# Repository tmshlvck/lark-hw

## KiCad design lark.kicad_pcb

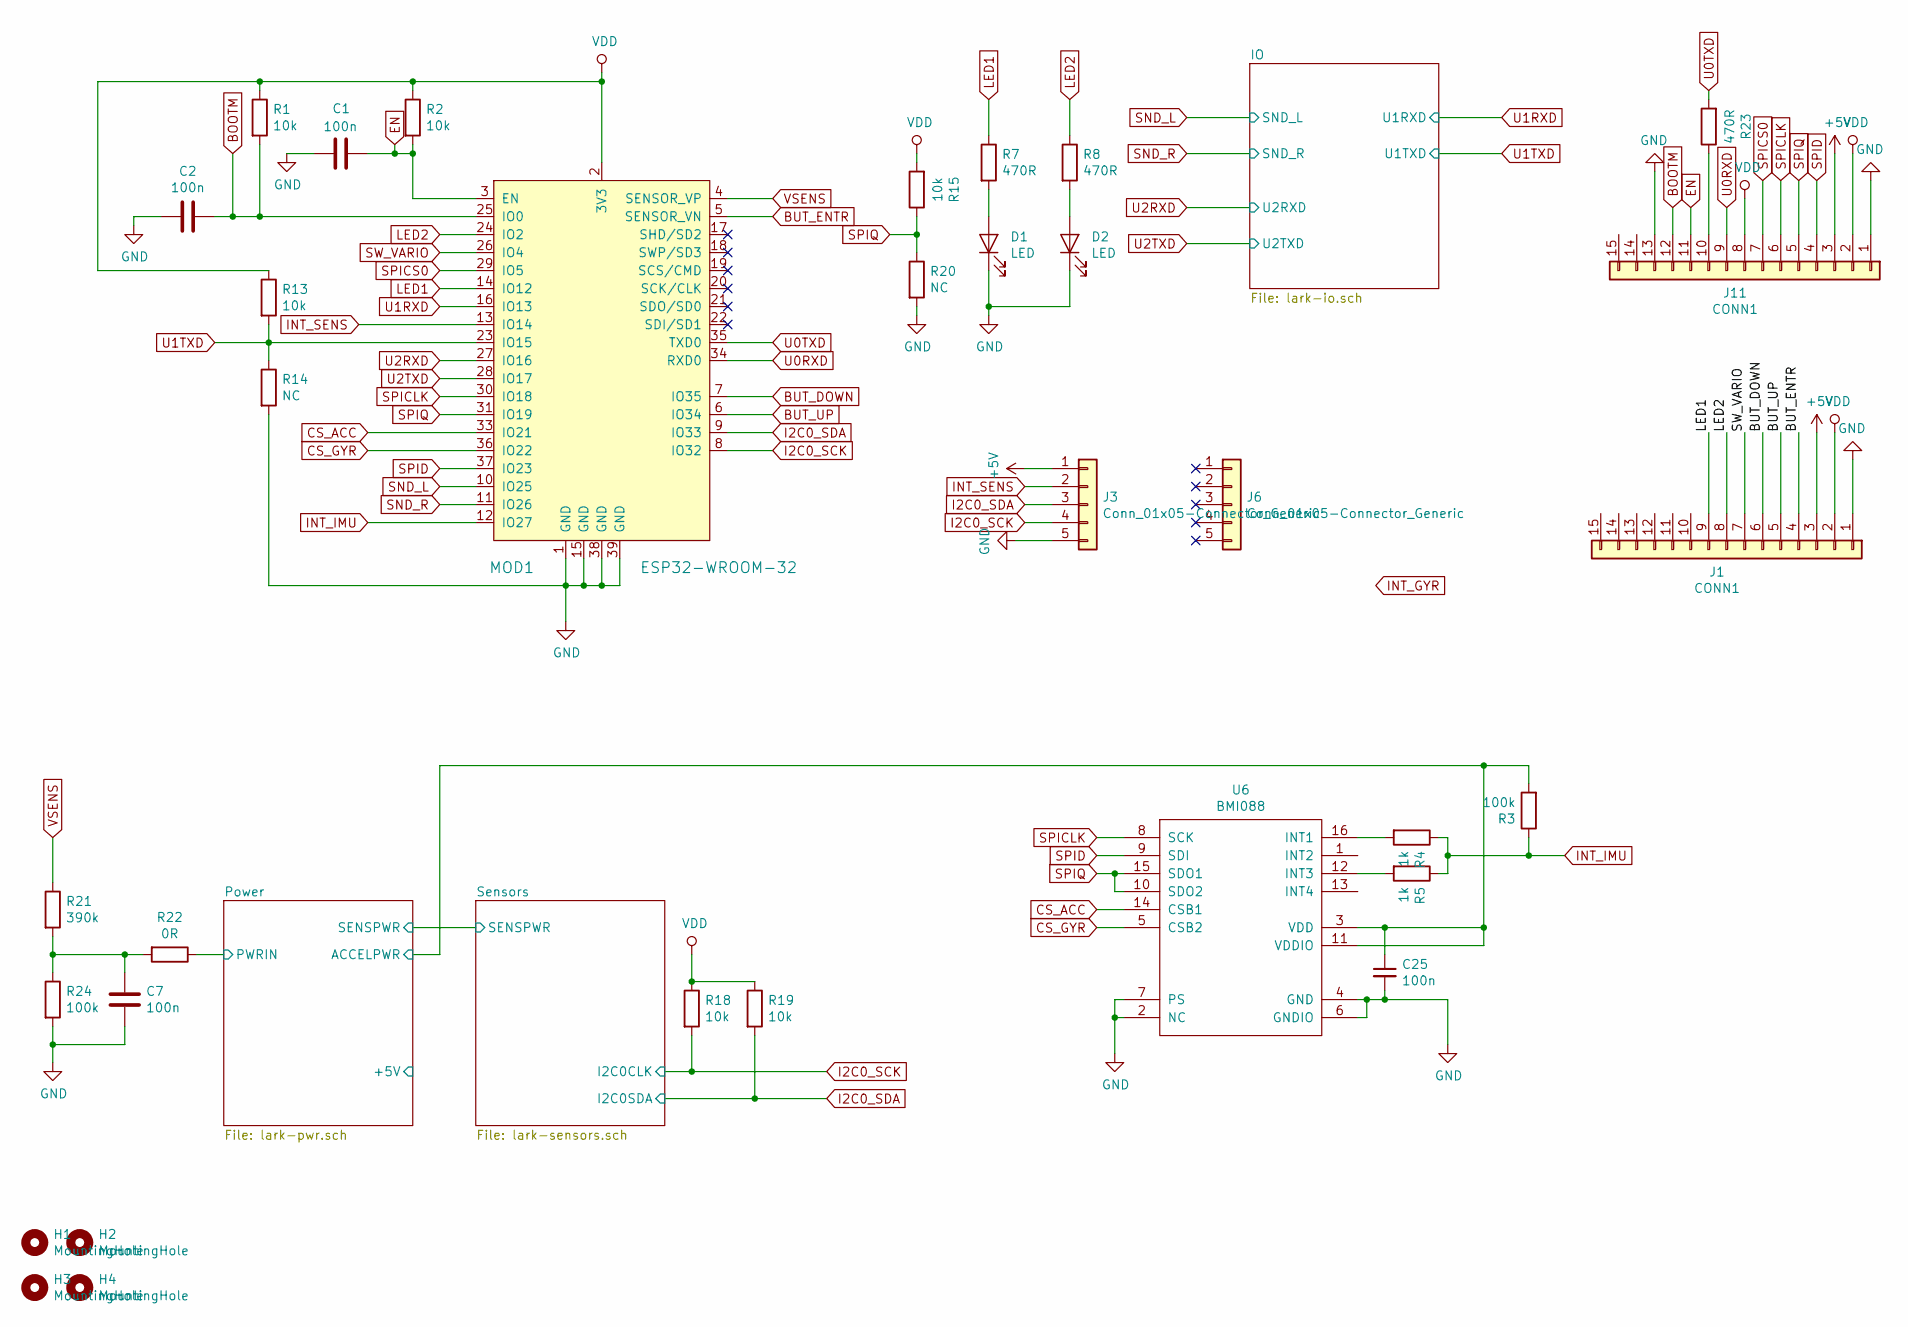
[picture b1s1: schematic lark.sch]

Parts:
C1, C2, C7: 100n; C_0805_2012Metric_Pad1.15x1.40mm_HandSolder; MPN 885012207128
C25: 100n; C_0805_2012Metric_Pad1.15x1.40mm_HandSolder
D1: LED; LED_1206_3216Metric_Pad1.42x1.75mm_HandSolder; MPN LTST-C150GKT
D2: LED; LED_1206_3216Metric_Pad1.42x1.75mm_HandSolder; MPN LTST-C150CKT
H1, H2, H3, H4: MountingHole; MountingHole_3.2mm_M3_DIN965
J1, J11: CONN1; PinHeader_1x15_P2.54mm_Vertical
J3, J6: Conn_01x05-Connector_Generic; PinHeader_1x05_P2.54mm_Vertical
MOD1: ESP32-WROOM-32; ESP32-WROOM-32D; MPN ESP32-WROOM-32; Digi-Key_PN 1904-1010-1-ND
R1, R2, R13, R15, R18, R19: 10k; R_0805_2012Metric_Pad1.15x1.40mm_HandSolder; MPN RC0805FR-0710KL
R3: 100k; R_0805_2012Metric_Pad1.15x1.40mm_HandSolder
R4, R5: 1k; R_0805_2012Metric_Pad1.15x1.40mm_HandSolder
R7, R8, R23: 470R; R_0805_2012Metric_Pad1.15x1.40mm_HandSolder; MPN RC0805FR-07470RL
R14, R20: NC; R_0805_2012Metric_Pad1.15x1.40mm_HandSolder
R21: 390k; R_0805_2012Metric_Pad1.15x1.40mm_HandSolder; MPN RT0805BRD07390KL
R22: 0R; R_0805_2012Metric_Pad1.15x1.40mm_HandSolder; MPN RC0805JR-070RL
R24: 100k; R_0805_2012Metric_Pad1.15x1.40mm_HandSolder; MPN RT0805BRD07100KL
U6: BMI088; LGA-16_handsolder

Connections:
+5V: J1.3, J3.1, J11.3; also elsewhere on the board
/Power/ACCELPWR: C25.1, R3.2, U6.3 (VDD), U6.11 (VDDIO); also elsewhere on the board
BOOTM: C2.1, J11.12, MOD1.25 (IO0), R1.2
BUT_DOWN: J1.6, MOD1.7 (IO35)
BUT_ENTR: J1.4, MOD1.5 (SENSOR_VN)
BUT_UP: J1.5, MOD1.6 (IO34)
CS_ACC: MOD1.33 (IO21), U6.14 (CSB1)
CS_GYR: MOD1.36 (IO22), U6.5 (CSB2)
EN: C1.1, J11.11, MOD1.3 (EN), R2.2
GND: C1.2, C2.2, C7.2, C25.2, D1.1 (K), D2.1 (K), J1.1, J3.5, J11.1, J11.13, MOD1.1 (GND), MOD1.15 (GND), MOD1.38 (GND), MOD1.39 (GND), R14.2, R20.2, R24.2, U6.2 (NC), U6.4 (GND), U6.6 (GNDIO), U6.7 (PS); also elsewhere on the board
I2C0_SCK: J3.4, MOD1.8 (IO32), R18.2; also elsewhere on the board
I2C0_SDA: J3.3, MOD1.9 (IO33), R19.2; also elsewhere on the board
INT_IMU: MOD1.12 (IO27), R3.1, R4.1, R5.1
INT_SENS: J3.2, MOD1.13 (IO14)
LED1: J1.9, MOD1.14 (IO12), R7.1
LED2: J1.8, MOD1.24 (IO2), R8.1
unnamed: C7.1, R21.2, R22.2, R24.1
unnamed: D1.2 (A), R7.2
unnamed: D2.2 (A), R8.2
unnamed: J11.10, R23.1
unnamed: R4.2, U6.16 (INT1)
unnamed: R5.2, U6.12 (INT3)
SND_L: MOD1.10 (IO25); also elsewhere on the board
SND_R: MOD1.11 (IO26); also elsewhere on the board
SPICLK: J11.6, MOD1.30 (IO18), U6.8 (SCK)
SPICS0: J11.7, MOD1.29 (IO5)
SPID: J11.4, MOD1.37 (IO23), U6.9 (SDI)
SPIQ: J11.5, MOD1.31 (IO19), R15.1, R20.1, U6.10 (SDO2), U6.15 (SDO1)
SW_VARIO: J1.7, MOD1.26 (IO4)
U0RXD: J11.9, MOD1.34 (RXD0)
U0TXD: MOD1.35 (TXD0), R23.2
U1RXD: MOD1.16 (IO13); also elsewhere on the board
U1TXD: MOD1.23 (IO15), R13.2, R14.1; also elsewhere on the board
U2RXD: MOD1.27 (IO16); also elsewhere on the board
U2TXD: MOD1.28 (IO17); also elsewhere on the board
VDD: J1.2, J11.2, J11.8, MOD1.2 (3V3), R1.1, R2.1, R13.1, R15.2, R18.1, R19.1; also elsewhere on the board
VSENS: MOD1.4 (SENSOR_VP), R21.1

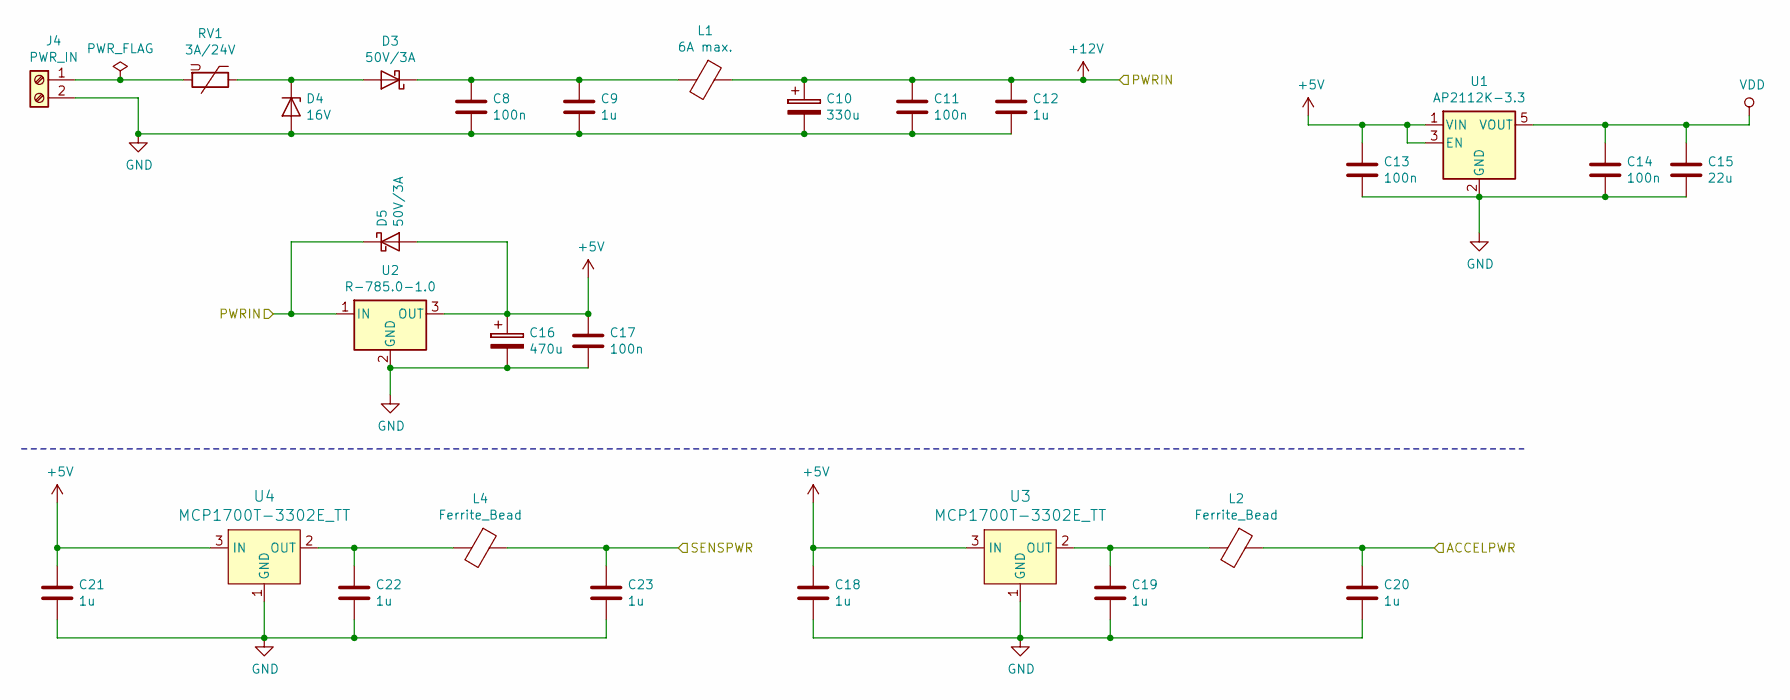
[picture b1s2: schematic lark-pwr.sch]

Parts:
C8, C11, C13, C14, C17: 100n; C_0805_2012Metric_Pad1.15x1.40mm_HandSolder; MPN 885012207128
C9, C12, C18, C19, C20, C21, C22, C23: 1u; C_0805_2012Metric_Pad1.15x1.40mm_HandSolder; MPN CL21B105KBFNNNG
C10: 330u; CP_Elec_10x10; MPN UUE1H331MNS1MS
C15: 22u; C_0805_2012Metric_Pad1.15x1.40mm_HandSolder; MPN GRM21BD70J226ME44L
C16: 470u; CP_Elec_10x10; MPN 493-16063-1-ND
D3, D5: 50V/3A; D_SOD-123; MPN SK35
D4: 16V; D_SOD-123; MPN SMBJ16A-TR
J4: PWR_IN; TerminalBlock_Phoenix_PT-1,5-2-3.5-H_1x02_P3.50mm_Horizontal; MPN 277-1721-ND
L1: 6A max.; L_1206_3216Metric_Pad1.42x1.75mm_HandSolder; MPN BLM31KN121SN1L
L2, L4: Ferrite_Bead; L_0805_2012Metric_Pad1.15x1.40mm_HandSolder; MPN BLM21BD272SH1L
RV1: 3A/24V; Fuse_2920_7451Metric_Pad2.10x5.45mm_HandSolder; MPN 0ZCF0300BF2C
U1: AP2112K-3.3; SOT-23-5
U2: R-785.0-1.0; Converter_DCDC_RECOM_R-78E-0.5_THT
U3, U4: MCP1700T-3302E_TT; SOT-23; MPN MCP1700T-3302E/TT; Digi-Key_PN MCP1700T3302ETTCT-ND

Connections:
+5V: C13.1, C16.1, C17.1, C18.1, C21.1, D5.2 (A), U1.1 (VIN), U1.3 (EN), U2.3 (OUT), U3.3 (IN), U4.3 (IN); also elsewhere on the board
/Power/ACCELPWR: C20.1, L2.1; also elsewhere on the board
/Sensors/SENSPWR: C23.1, L4.1; also elsewhere on the board
GND: C8.2, C9.2, C10.2, C11.2, C12.2, C13.2, C14.2, C15.2, C16.2, C17.2, C18.2, C19.2, C20.2, C21.2, C22.2, C23.2, D4.2 (A), J4.2, U1.2 (GND), U2.2 (GND), U3.1 (GND), U4.1 (GND); also elsewhere on the board
unnamed: C19.1, L2.2, U3.2 (OUT)
unnamed 43: J4.1, RV1.2; also elsewhere on the board
VDD: C14.1, C15.1, U1.5 (VOUT); also elsewhere on the board

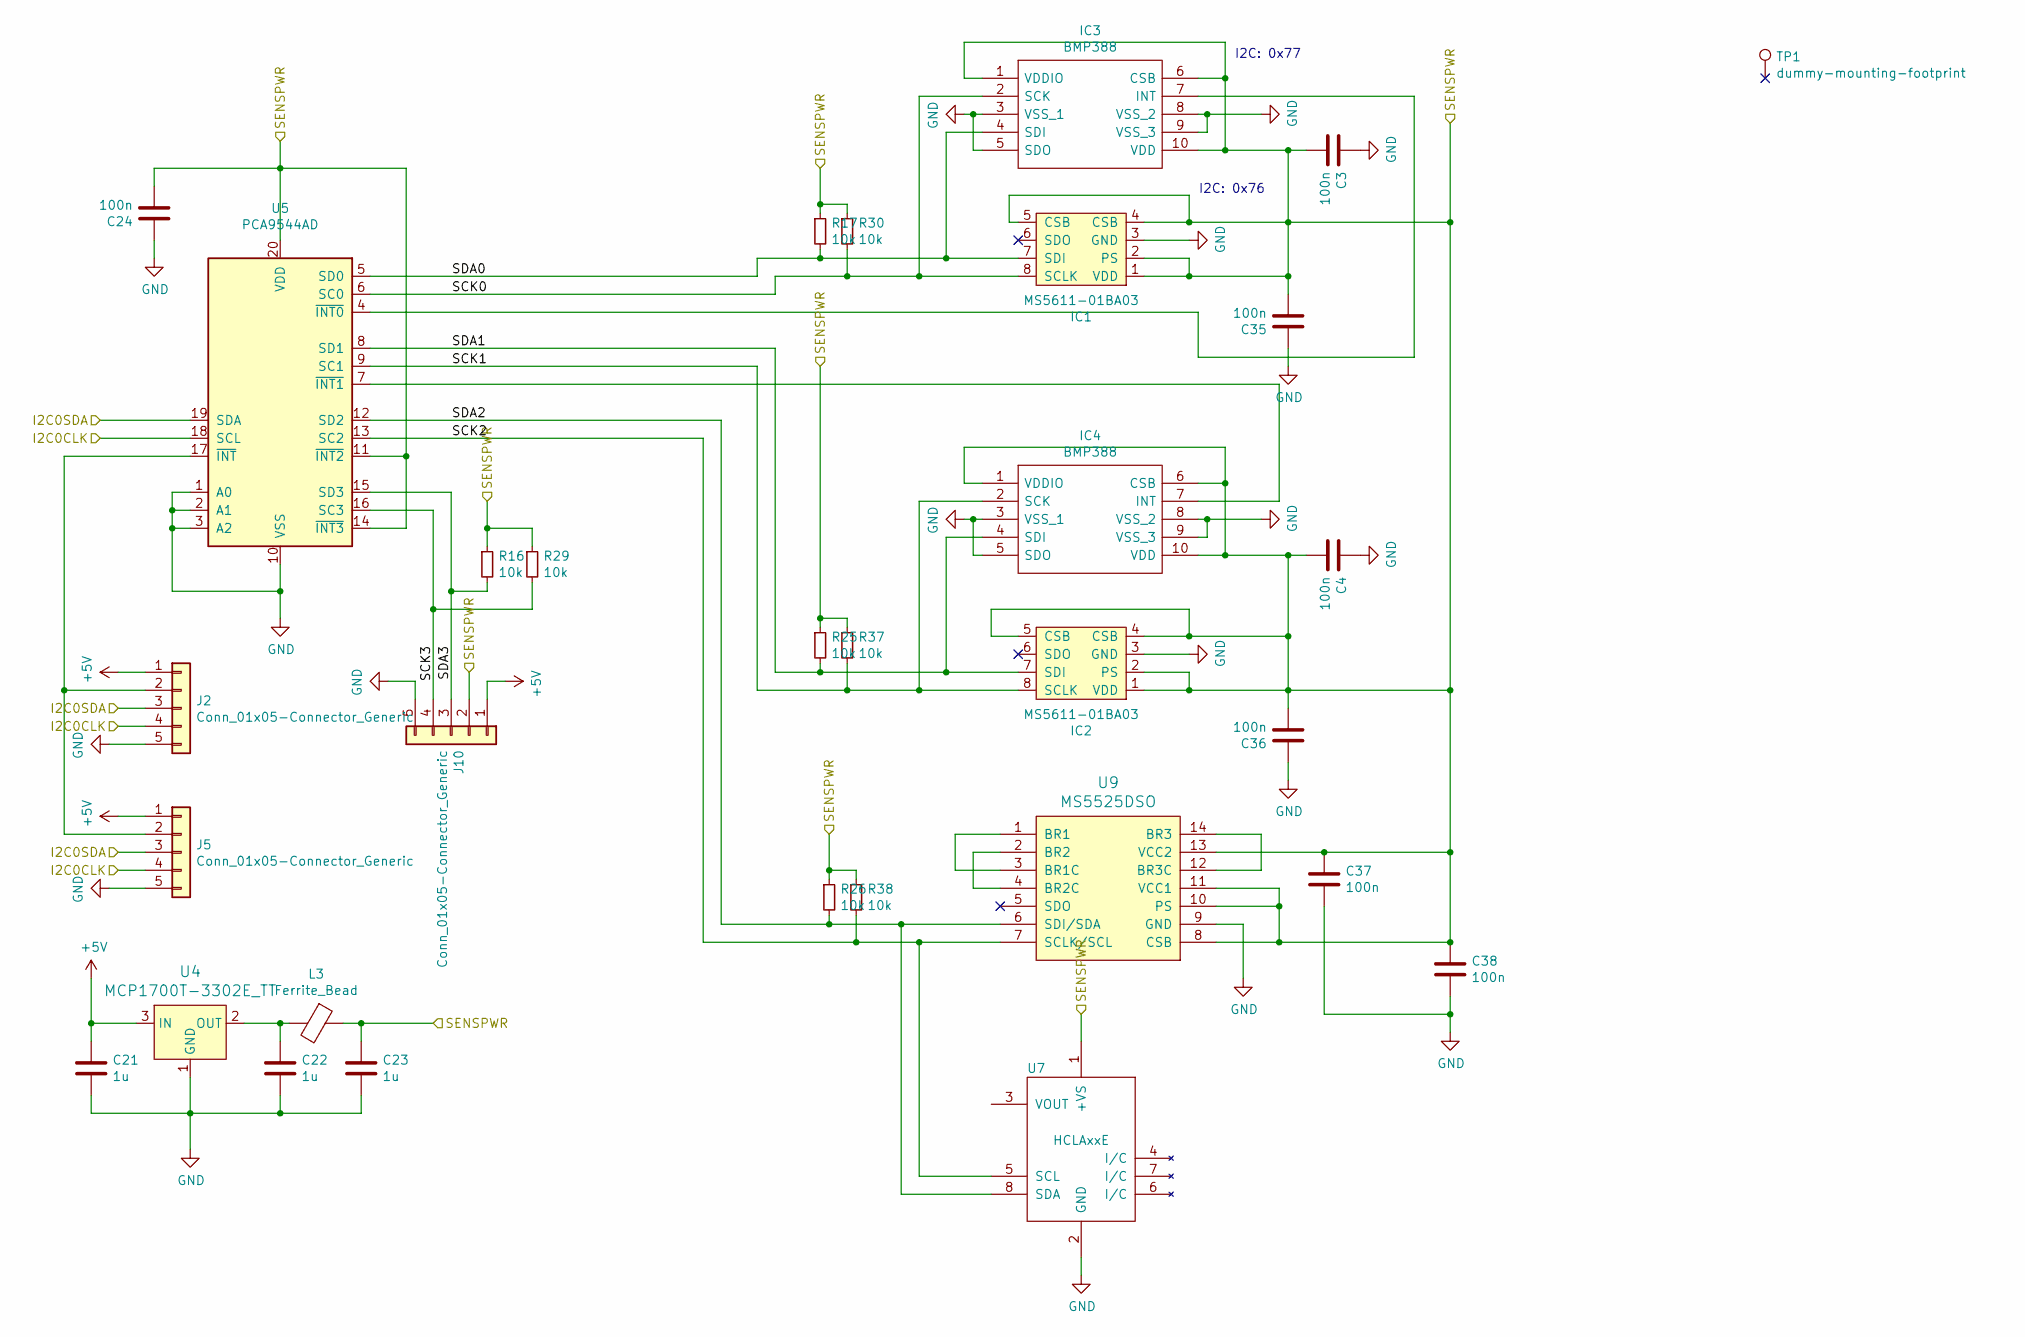
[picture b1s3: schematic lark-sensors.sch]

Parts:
C3, C4: 100n; C_0603_1608Metric; MPN 885012207128
C21, C22, C23: 1u; C_0805_2012Metric_Pad1.15x1.40mm_HandSolder; MPN CL21B105KBFNNNG
C24, C35, C36, C37, C38: 100n; C_0805_2012Metric_Pad1.15x1.40mm_HandSolder; MPN 885012207128
IC1, IC2: MS5611-01BA03; LGA-8_3x5mm_P1.25mm_handsolder; MPN MS561101BA03-50; Farnell 2362662
IC3, IC4: BMP388; LGA-10_2.0x2.0x0.75_handsolder; Manufacturer_Part_Number BMP388; Mouser Part Number 262-BMP388
J2, J5, J10: Conn_01x05-Connector_Generic; PinHeader_1x05_P2.54mm_Vertical
L3: Ferrite_Bead; L_0805_2012Metric_Pad1.15x1.40mm_HandSolder; MPN BLM21BD272SH1L
R16, R17, R25, R26, R29, R30, R37, R38: 10k; R_0805_2012Metric_Pad1.15x1.40mm_HandSolder
TP1: dummy-mounting-footprint; lark_sensor_mount
U4: MCP1700T-3302E_TT; SOT-23; MPN MCP1700T-3302E/TT; Digi-Key_PN MCP1700T3302ETTCT-ND
U5: PCA9544AD; SOIC-20W_7.5x12.8mm_P1.27mm
U7: HCLAxxE
U9: MS5525DSO; SOIC-14W_7.5x9.0mm_P1.27mm; MPN 5525DSO-DB001DS

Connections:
+5V: C21.1, J2.1, J5.1, J10.1, U4.3 (IN); also elsewhere on the board
/Sensors/SCK0: IC1.8 (SCLK), IC3.2 (SCK), R30.2, U5.6 (SC0)
/Sensors/SCK1: IC2.8 (SCLK), IC4.2 (SCK), R37.2, U5.9 (SC1)
/Sensors/SCK2: R38.2, U5.13 (SC2), U7.5 (SCL), U9.7 (SCLK/SCL)
/Sensors/SCK3: J10.4, R29.2, U5.16 (SC3)
/Sensors/SDA0: IC1.7 (SDI), IC3.4 (SDI), R17.2, U5.5 (SD0)
/Sensors/SDA1: IC2.7 (SDI), IC4.4 (SDI), R25.2, U5.8 (SD1)
/Sensors/SDA2: R26.2, U5.12 (SD2), U7.8 (SDA), U9.6 (SDI/SDA)
/Sensors/SDA3: J10.3, R16.2, U5.15 (SD3)
/Sensors/SENSPWR: C3.2, C4.2, C23.1, C24.2, C35.2, C36.2, C37.1, C38.1, IC1.1 (VDD), IC1.2 (PS), IC1.4 (CSB), IC1.5 (CSB), IC2.1 (VDD), IC2.2 (PS), IC2.4 (CSB), IC2.5 (CSB), IC3.1 (VDDIO), IC3.6 (CSB), IC3.10 (VDD), IC4.1 (VDDIO), IC4.6 (CSB), IC4.10 (VDD), J10.2, L3.1, R16.1, R17.1, R25.1, R26.1, R29.1, R30.1, R37.1, R38.1, U5.11 (~INT2), U5.14 (~INT3), U5.20 (VDD), U7.1 (+VS), U9.8 (CSB), U9.10 (PS), U9.11 (VCC1), U9.13 (VCC2); also elsewhere on the board
GND: C3.1, C4.1, C21.2, C22.2, C23.2, C24.1, C35.1, C36.1, C37.2, C38.2, IC1.3 (GND), IC2.3 (GND), IC3.3 (VSS_1), IC3.5 (SDO), IC3.8 (VSS_2), IC3.9 (VSS_3), IC4.3 (VSS_1), IC4.5 (SDO), IC4.8 (VSS_2), IC4.9 (VSS_3), J2.5, J5.5, J10.5, U4.1 (GND), U5.1 (A0), U5.2 (A1), U5.3 (A2), U5.10 (VSS), U7.2 (GND), U9.9 (GND); also elsewhere on the board
I2C0_SCK: J2.4, J5.4, U5.18 (SCL); also elsewhere on the board
I2C0_SDA: J2.3, J5.3, U5.19 (SDA); also elsewhere on the board
unnamed: IC3.7 (INT), U5.4 (~INT0)
unnamed: IC4.7 (INT), U5.7 (~INT1)
unnamed: J2.2, J5.2, U5.17 (~INT)
unnamed: U9.1 (BR1), U9.3 (BR1C)
unnamed: U9.2 (BR2), U9.4 (BR2C)
unnamed: U9.12 (BR3C), U9.14 (BR3)

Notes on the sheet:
I2C: 0x77
I2C: 0x76

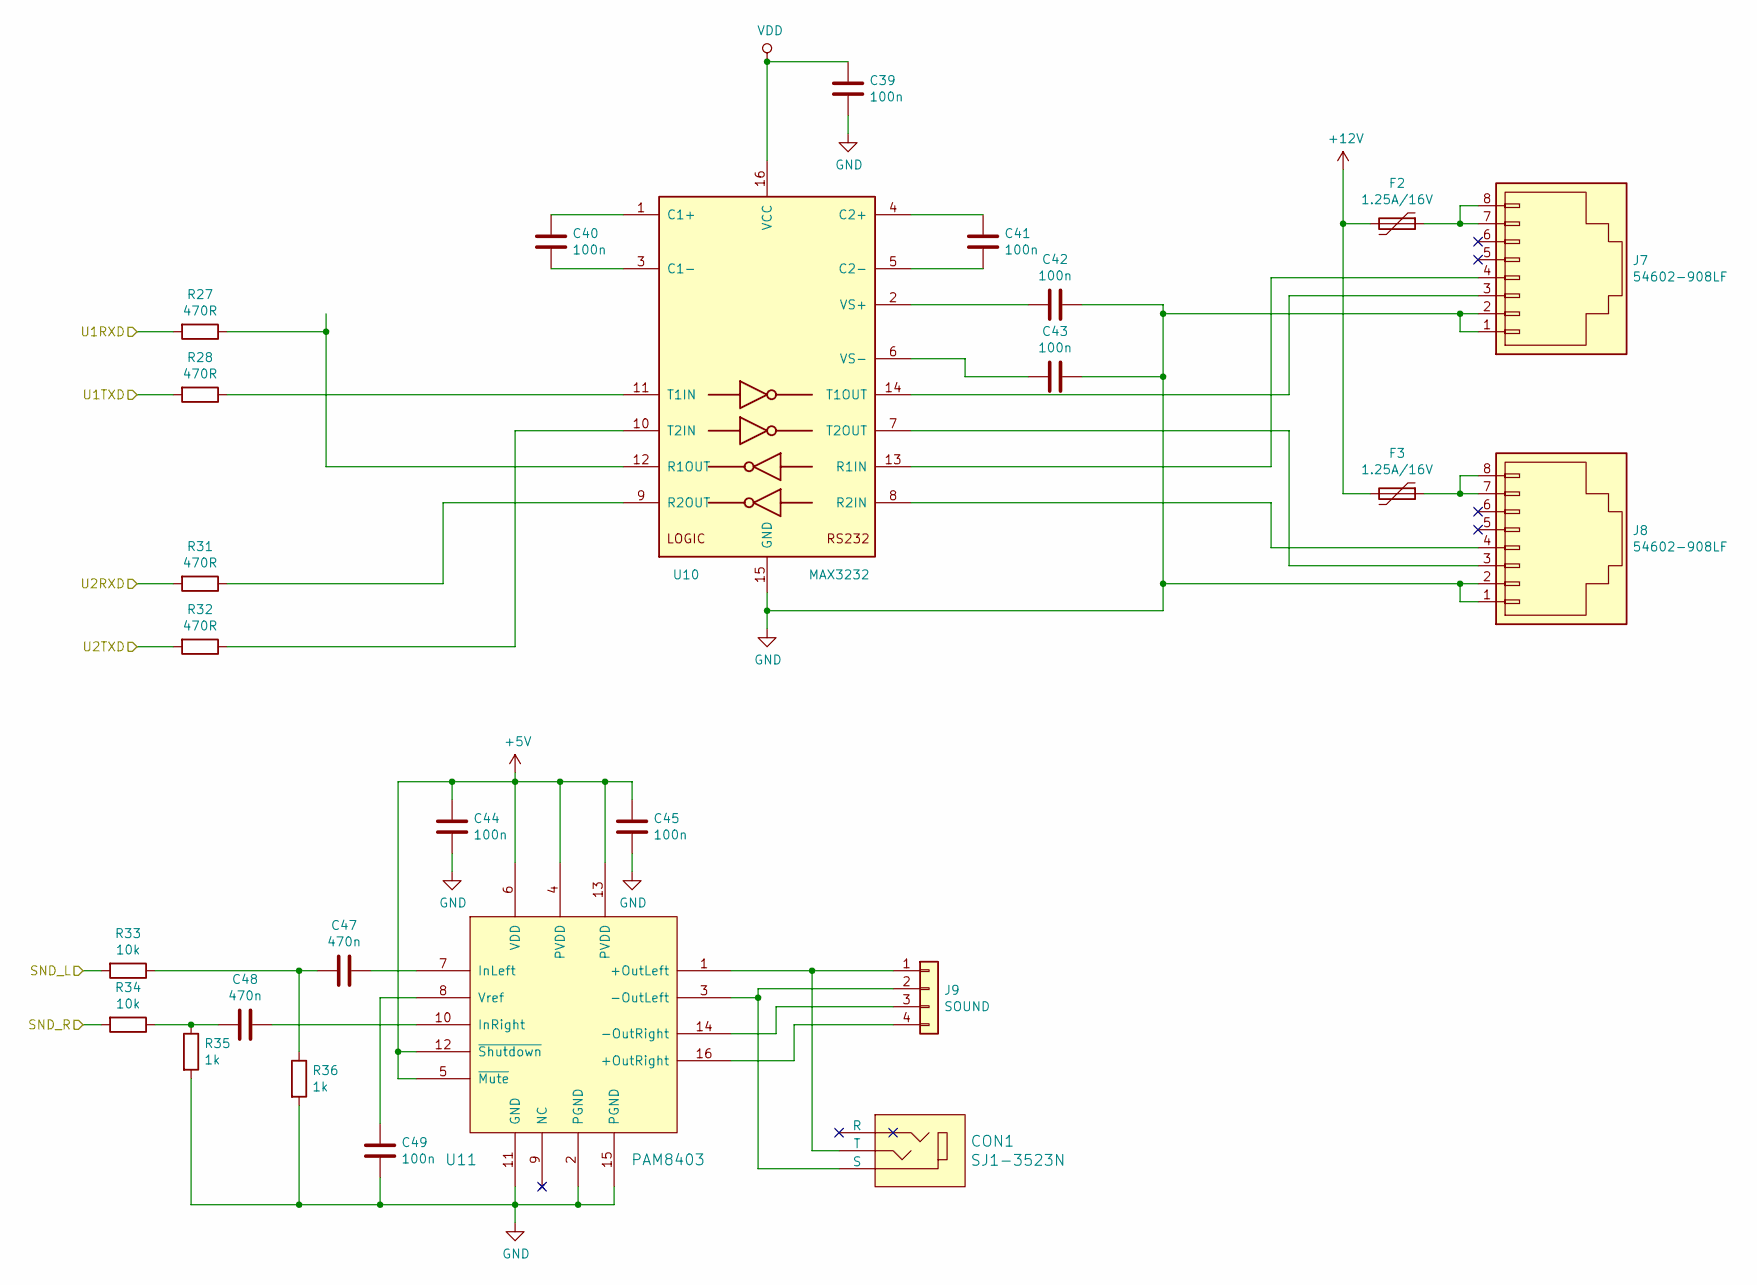
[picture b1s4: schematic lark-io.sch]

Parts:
C39, C40, C41, C42, C43, C44, C45, C49: 100n; C_0805_2012Metric_Pad1.15x1.40mm_HandSolder; MPN 885012207128
C47, C48: 470n; C_0805_2012Metric_Pad1.15x1.40mm_HandSolder; MPN 885012207102
CON1: SJ1-3523N; Headphone_Jack_2.5mm_SJ1-3523N; MPN SJ1-3523N; Digi-Key_PN CP1-3523N-ND
F2, F3: 1.25A/16V; Fuse_1812_4532Metric_Pad1.30x3.40mm_HandSolder; MPN 1812L125/16DR
J7, J8: 54602-908LF; 634108185521; MPN 54602-908LF; Digi-Key_PN 609-1046-ND
J9: SOUND; PinHeader_1x04_P2.54mm_Vertical
R27, R28, R31, R32: 470R; R_0805_2012Metric_Pad1.15x1.40mm_HandSolder; MPN RC0805FR-07470RL
R33, R34: 10k; R_0805_2012Metric_Pad1.15x1.40mm_HandSolder; MPN RC0805FR-0710KL
R35, R36: 1k; R_0805_2012Metric_Pad1.15x1.40mm_HandSolder; MPN RC0805FR-071KL
U10: MAX3232; SOIC-16_3.9x9.9mm_P1.27mm; MPN MAX3232ECDR
U11: PAM8403; SOIC-16_3.9x9.9mm_P1.27mm; MPN PAM8403DR

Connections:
+5V: C44.1, C45.1, U11.4 (PVDD), U11.5 (~Mute), U11.6 (VDD), U11.12 (~Shutdown), U11.13 (PVDD); also elsewhere on the board
GND: C39.2, C42.1, C43.1, C44.2, C45.2, C49.2, J7.1, J7.2, J8.1, J8.2, R35.2, R36.2, U10.15 (GND), U11.2 (PGND), U11.11 (GND), U11.15 (PGND); also elsewhere on the board
unnamed: C40.1, U10.1 (C1+)
unnamed: C40.2, U10.3 (C1-)
unnamed: C41.1, U10.4 (C2+)
unnamed: C41.2, U10.5 (C2-)
unnamed: C42.2, U10.2 (VS+)
unnamed: C43.2, U10.6 (VS-)
unnamed: C47.1, U11.7 (InLeft)
unnamed: C47.2, R33.1, R36.1
unnamed: C48.1, U11.10 (InRight)
unnamed: C48.2, R34.1, R35.1
unnamed: C49.1, U11.8 (Vref)
unnamed: CON1.1 (S), J9.2, U11.3 (-OutLeft)
unnamed: CON1.2 (T), J9.1, U11.1 (+OutLeft)
unnamed: F2.1, J7.7, J7.8
unnamed: F3.1, J8.7, J8.8
unnamed: J7.3, U10.14 (T1OUT)
unnamed: J7.4, U10.13 (R1IN)
unnamed: J8.3, U10.7 (T2OUT)
unnamed: J8.4, U10.8 (R2IN)
unnamed: J9.3, U11.14 (-OutRight)
unnamed: J9.4, U11.16 (+OutRight)
unnamed: R27.1, U10.12 (R1OUT)
unnamed: R28.1, U10.11 (T1IN)
unnamed: R31.1, U10.9 (R2OUT)
unnamed: R32.1, U10.10 (T2IN)
SND_L: R33.2; also elsewhere on the board
SND_R: R34.2; also elsewhere on the board
U1RXD: R27.2; also elsewhere on the board
U1TXD: R28.2; also elsewhere on the board
U2RXD: R31.2; also elsewhere on the board
U2TXD: R32.2; also elsewhere on the board
VDD: C39.1, U10.16 (VCC); also elsewhere on the board

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
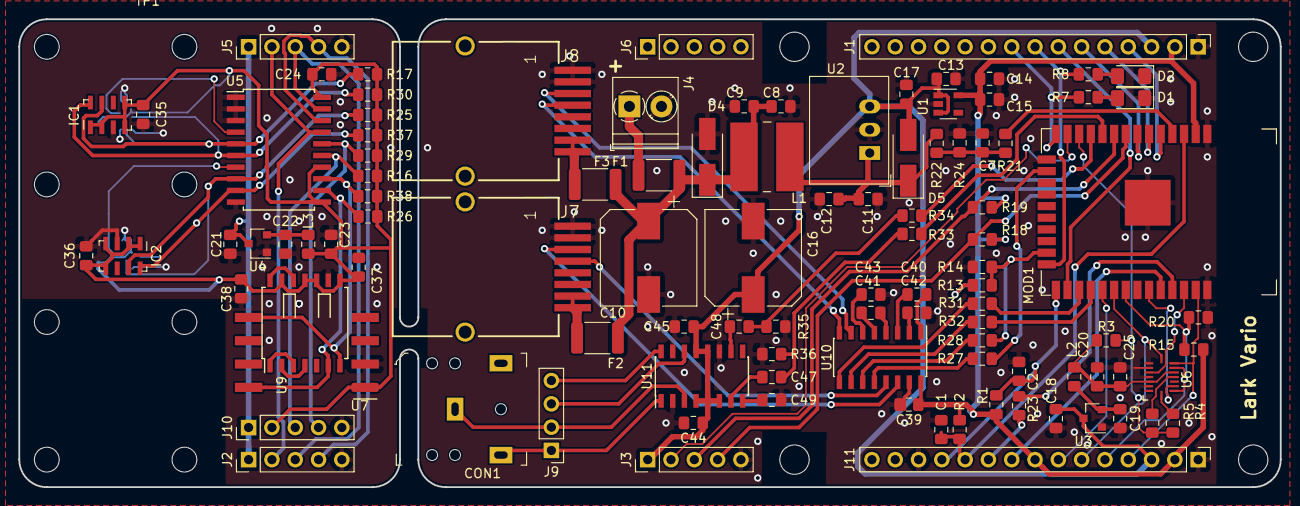
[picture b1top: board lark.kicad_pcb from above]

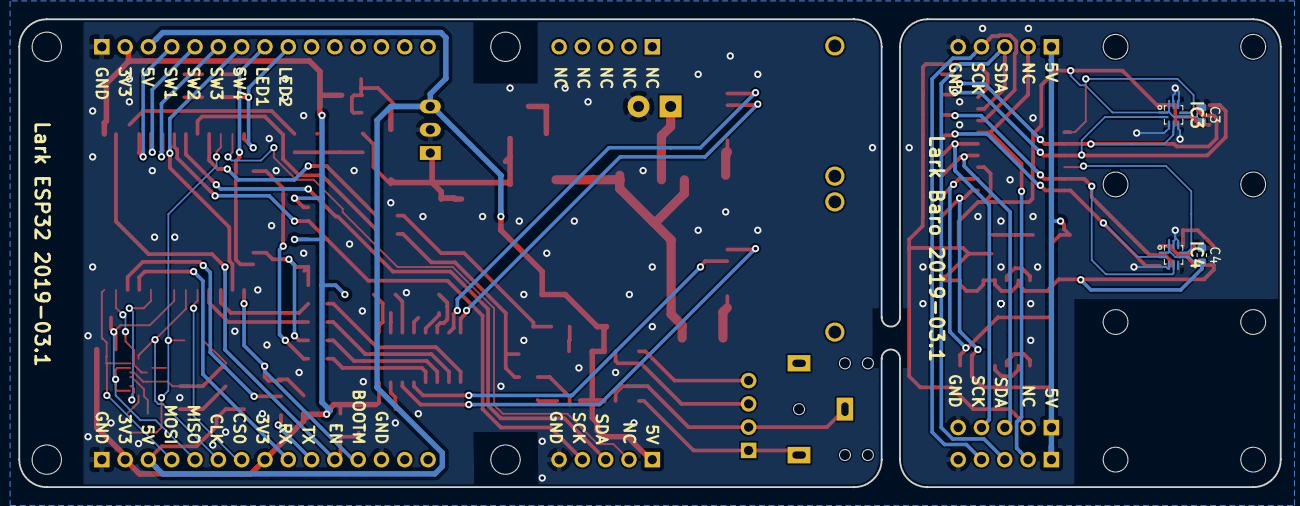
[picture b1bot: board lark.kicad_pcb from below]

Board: 2 copper layers, 137.5 x 51.0 mm, 112 parts (4 on the bottom side), 82 nets.

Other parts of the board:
F1: 3A/24V; Fuse_1812_4532Metric_Pad1.30x3.40mm_HandSolder

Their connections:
unnamed 43: F1.2; also elsewhere on the board

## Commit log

2018-01-24 Add first version of schematic
    Add first version of the schematic.
    TODOs:
    Select passive parts
    Verify digital interconnects
    Review power supplies
    Review decoupling, EMI-relevant parts...
2018-01-24 Remove orphan GPS PPS signal
    Remove orphan.
    Give up on GPS PPS feed. Not enough pins.
2018-03-23 Finalize schematics and component selection
    Remove SD interface
    Rework power supplies
2019-02-03 Rework the schematic from scratch
    Rework basic ESP32 pin assignment
    Rework power supply
    Rework interface
    Rework sound generation - remove I2C codec, use internal DAC
    Add D-class amplifier
    Add Serial lines
2019-02-08 Finalize schematic
    Finish part selection
    Pending issues: IMU, switches & LEDs, mechanical parts and housing
    selection.
2019-02-15 Prepare symbol for BMX055
    MPU-9250 is being phased out... We need a replacement IMU.
2019-02-16 Replace MPU-9250 IMU with BMX055
2019-02-16 Fix TPS2511 thermal pad number
    PAD is pin 9.
2019-02-16 Fill in all remaining PNs in the schematics
    Finish the part selection, let's hope for least possible number of mistakes.
2019-02-20 Add initial layout of the board.
    Think over the placement of the parts and perhaps reduce unnecessary capacitors in the power supplies.
2019-03-10 Intermediate status while arranging compontents.
    Manually grouped components into smaller islands.
    Some parts were changed:
    * U1: SOT-23-3 LDO should be sufficient
    * CP_Elec: Use 10x10 size
2019-03-14 continue layout work, WIP
2019-03-14 update layout
    IRQs connected
    somehow handsoldering friendly BS5611
    DRC is OK.
    Unconnected: 5 nets (will later connect the sensor board)
2019-03-14 Use BMI088 instead of BMX055.
    Symbol for BMI088 was created and placed in the schematic.
    Still looking for a LGA-16 4.5x3.0 footprint. Do we really need to
    create that ourselves?
2019-03-14 Layout almost complete.
2019-03-14 import BMP388
2019-03-14 Fitting layout into 57 mm instrument.
    * board width is 51 mm at the moment
    * split into two boards (sensor and main) which can be stacked with
    2.54 mm pinheaders.
    * ESP32 was put to bottom with optional pcb antenna facing to front.
    * added footprint for optional HCLAxxE on sensorboard
    * added footprint for BMI088
2019-03-14 connect SENS_INT and IMU_INT to ESP
2019-03-14 connect BMI088 INT lines
    They will be set to open-drain mode, so one interrupt pin on the ESP32
    can be used for both.
2019-03-14 variant of MS5611 footprint for easier handsoldering
2019-03-14 Updating schematic for the first prototype
    * U1 can supply up to 600 mA
    * drop USB charger for now
    * smaller type of DC/DC (U2) for input
    * remove one of the large capacitors
    * change BMX interface to 4-wire SPI for speed reasons
    * add I2C mux for pressure sensors
2019-03-14 sensors.sch: connect INT pins of BMP388 to I2C mux.
2019-03-14 lib: add LGA-10 footprint (for BMP388)
2019-03-14 fix some vias
    they were not shown correctly in the preview on aisler.net
2019-03-14 even more finished
2019-03-14 Plot schematic and save in out
    Plot the prototype schematic and save in out directory.
